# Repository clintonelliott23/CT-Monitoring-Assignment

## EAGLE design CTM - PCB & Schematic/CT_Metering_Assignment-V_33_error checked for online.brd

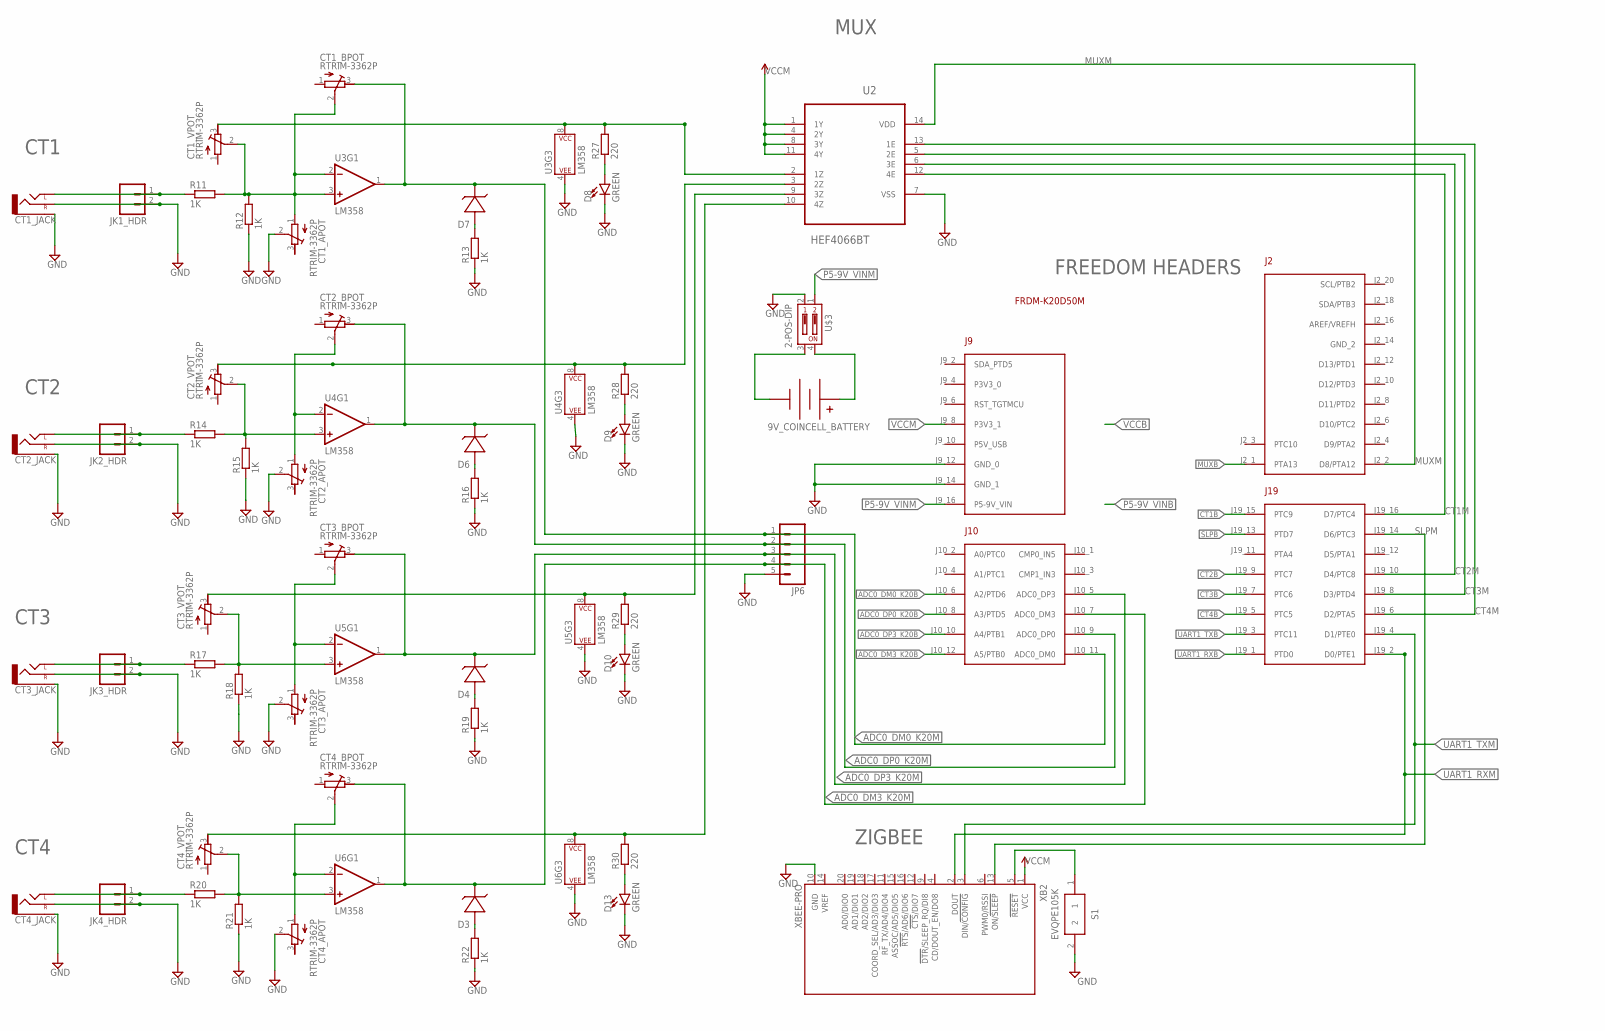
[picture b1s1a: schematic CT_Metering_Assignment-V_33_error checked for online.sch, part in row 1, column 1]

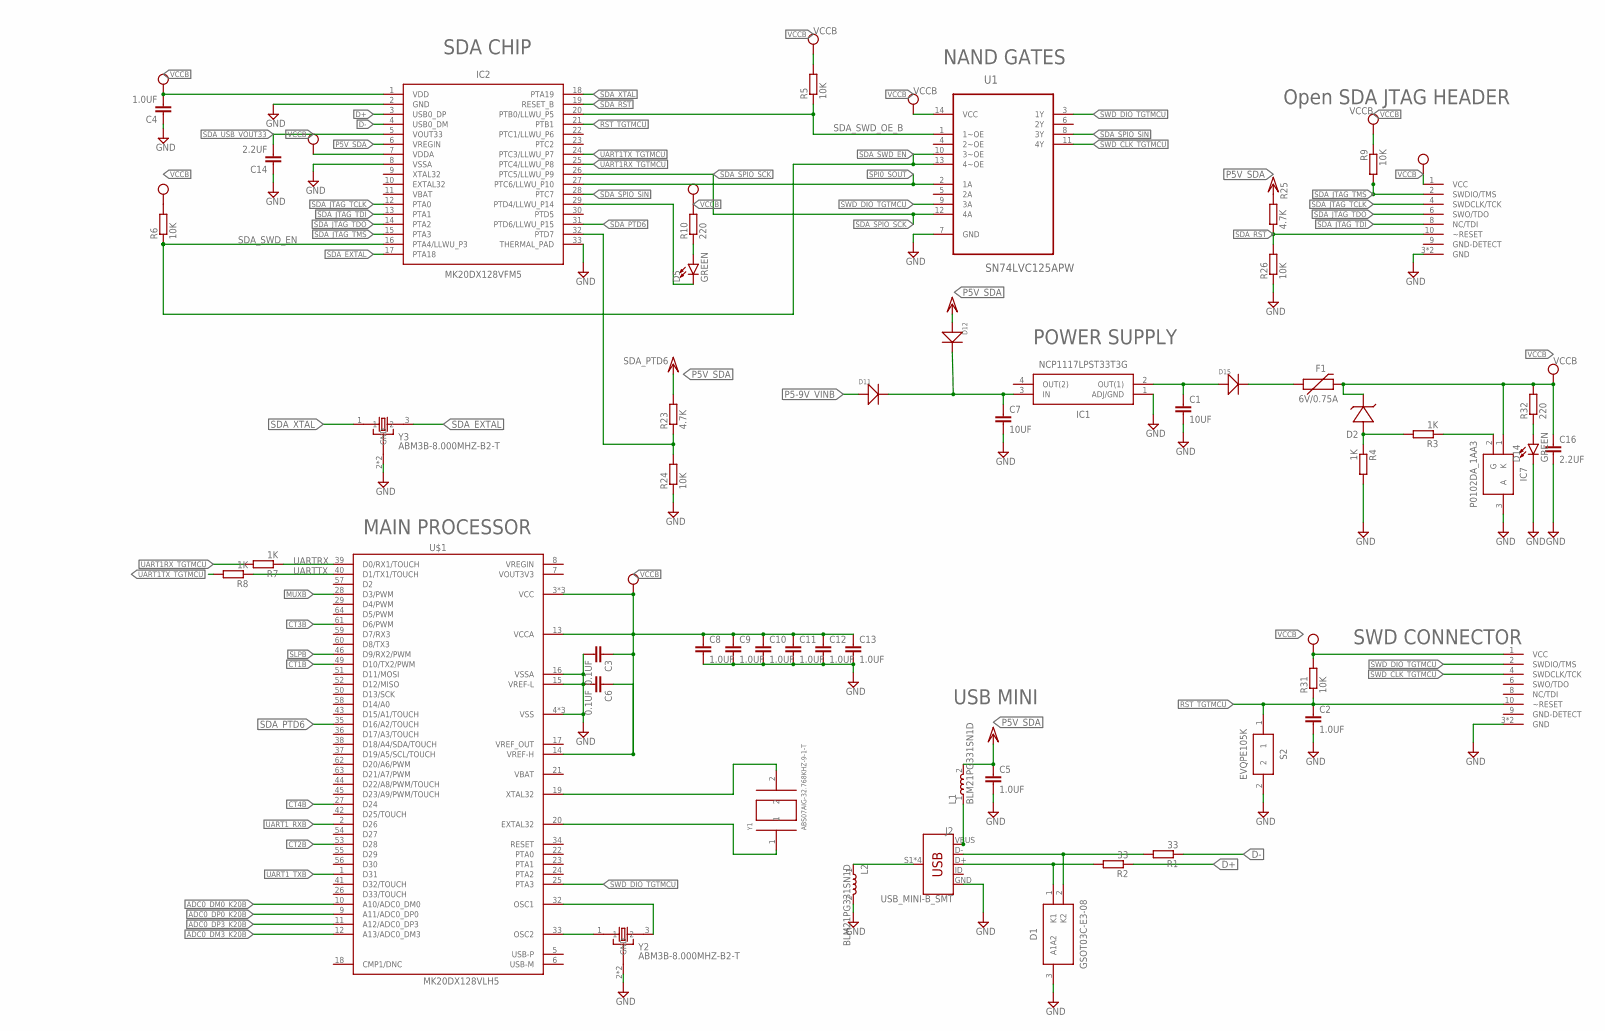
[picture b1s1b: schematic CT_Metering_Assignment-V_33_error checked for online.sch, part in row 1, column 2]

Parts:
9V_COINCELL_BATTERY: BC9VPC
C1, C7: 10UF; C1210
C2, C4, C5, C8, C9, C10, C11, C12, C13: 1.0UF; C1210
C3, C6: 0.1UF; C1210
C14, C16: 2.2UF; C1210
CT1_APOT, CT1_BPOT, CT1_VPOT, CT2_APOT, CT2_BPOT, CT2_VPOT, CT3_APOT, CT3_BPOT, CT3_VPOT, CT4_APOT, CT4_BPOT, CT4_VPOT: RTRIM-3362P; RTRIM3362P
CT1_JACK, CT2_JACK, CT3_JACK, CT4_JACK: AUDIO-JACKPTH; AUDIO-JACK
D1: GSOT03C-E3-08; SOT100P248X115-3N
D2, D3, D4, D6, D7: ZENER; SOD123
D5, D8, D9, D10, D13, D14: GREEN; LED-0603
D11, D12, D15: 20V-1A; SOD-123
F1: 6V/0.75A; 1206
FRDM1: FRDM-K20D50M
IC1: NCP1117LPST33T3G; SOT230P700X180-4N
IC2: MK20DX128VFM5; SOT617-14
IC7: P0102DA_1AA3; TO-92
J2: USB_MINI-B_SMT; USB-MINIB
JK1_HDR, JK2_HDR, JK3_HDR, JK4_HDR: M02PTH; 1X02
JP6: M05PTH; 1X05
L1, L2: BLM21PG331SN1D; INDC2012X87
R1, R2: 33; PRL1632
R3, R4, R7, R8, R11, R12, R13, R14, R15, R16, R17, R18, R19, R20, R21, R22: 1K; PRL1632
R5, R6, R9, R24, R26, R31: 10K; PRL1632
R10, R27, R28, R29, R30, R32: 220; PRL1632
R23, R25: 4.7K; PRL1632
S1, S2: EVQPE105K; EVQPE1
U1: SN74LVC125APW; SOP65P640X120-14N
U2: HEF4066BT; SOIC127P600X175-14N
U3, U4, U5, U6: LM358; DIP08
U$1: MK20DX128VLH5; QFP50P1200X1200X160-64N
U$2: 2X5_0.05"_CORTEX_DEBUGTH_NOKEY_UNSHROUDED; 2X5_0.05"_TH_NS
U$3: 2-POS-DIP; CHS-02A
U$6: SWD HHEADER; 2X5_0.05"_TH_NS
XB2: XBEE-PRO
Y1: ABS07AIG-32.768KHZ-9-1-T; XTAL320X150X90
Y2, Y3: ABM3B-8.000MHZ-B2-T; OSCSC500X320X110-4N

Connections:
ADC0_DM0_K20B: FRDM1.J10_6 (A2/PTD6), U$1.10 (A10/ADC0_DM0)
ADC0_DM0_K20M: CT1_BPOT.3, D7.C (-), FRDM1.J10_11 (ADC0_DM0), JP6.1, U3.1 (OUT)
ADC0_DM3_K20B: FRDM1.J10_12 (A5/PTB0), U$1.12 (A13/ADC0_DM3)
ADC0_DM3_K20M: CT4_BPOT.3, D3.C (-), FRDM1.J10_7 (ADC0_DM3), JP6.4, U6.1 (OUT)
ADC0_DP0_K20B: FRDM1.J10_8 (A3/PTD5), U$1.9 (A11/ADC0_DP0)
ADC0_DP0_K20M: CT2_BPOT.3, D6.C (-), FRDM1.J10_9 (ADC0_DP0), JP6.2, U4.1 (OUT)
ADC0_DP3_K20B: FRDM1.J10_10 (A4/PTB1), U$1.11 (A12/ADC0_DP3)
ADC0_DP3_K20M: CT3_BPOT.3, D4.C (-), FRDM1.J10_5 (ADC0_DP3), JP6.3, U5.1 (OUT)
CT1B: FRDM1.J19_15 (PTC9), U$1.49 (D10/TX2/PWM)
CT1M: FRDM1.J19_16 (D7/PTC4), U2.12 (4E)
CT1_PWR: CT1_VPOT.3, R27.2, U2.2 (1Z), U3.8 (P$V+)
CT2B: FRDM1.J19_9 (PTC7), U$1.53 (D28)
CT2M: FRDM1.J19_10 (D4/PTC8), U2.6 (3E)
CT2_PWR: CT2_VPOT.3, R28.2, U2.3 (2Z), U4.8 (P$V+)
CT3B: FRDM1.J19_7 (PTC6), U$1.61 (D6/PWM)
CT3M: FRDM1.J19_8 (D3/PTD4), U2.5 (2E)
CT3_PWR: CT3_VPOT.3, R29.2, U2.9 (3Z), U5.8 (P$V+)
CT4B: FRDM1.J19_5 (PTC5), U$1.27 (D24)
CT4M: FRDM1.J19_6 (D2/PTA5), U2.13 (1E)
CT4_PWR: CT4_VPOT.3, R30.2, U2.10 (4Z), U6.8 (P$V+)
D+: IC2.3 (USB0_DP), R2.1
D-: IC2.4 (USB0_DM), R1.1
EXTAL32: U$1.20 (EXTAL32), Y1.1
GND: C1.2, C2.2, C3.2, C4.1, C5.2, C6.2, C7.2, C8.2, C9.2, C10.2, C11.2, C12.2, C13.2, C14.1, C16.2, CT1_APOT.2, CT1_JACK.RING (RIGHT), CT1_JACK.SLEEVE, CT2_APOT.2, CT2_JACK.RING (RIGHT), CT2_JACK.SLEEVE, CT3_APOT.2, CT3_JACK.RING (RIGHT), CT3_JACK.SLEEVE, CT4_APOT.2, CT4_JACK.RING (RIGHT), CT4_JACK.SLEEVE, D1.3 (A1A2), D8.C, D9.C, D10.C, D13.C, D14.C, FRDM1.J9_12 (GND_0), FRDM1.J9_14 (GND_1), IC1.1 (ADJ/GND), IC2.2 (GND), IC2.8 (VSSA), IC2.33 (THERMAL_PAD), IC7.3 (A), J2.GND, JK1_HDR.2, JK2_HDR.2, JK3_HDR.2, JK4_HDR.2, JP6.5, L2.2, R4.2, R12.1, R13.1, R15.1, R16.1, R18.1, R19.1, R21.1, R22.1, R24.1, R26.1, S1.2, S2.2, U1.7 (GND), U2.7 (VSS), U3.4 (P$V-), U4.4 (P$V-), U5.4 (P$V-), U6.4 (P$V-), U$1.4 (VSS), U$1.15 (VREF-L), U$1.16 (VSSA), U$1.31 (VSS), U$1.47 (VSS), U$2.3 (GND), U$2.5 (GND), U$3.2, U$6.3 (GND), U$6.5 (GND), XB2.10 (GND), Y2.2 (GND), Y2.4 (GND), Y3.2 (GND), Y3.4 (GND)
MUXB: FRDM1.J2_1 (PTA13), U$1.28 (D3/PWM)
MUXM: FRDM1.J2_2 (D8/PTA12), U2.14 (VDD)
unnamed: 9V_COINCELL_BATTERY.V-, U$3.3
unnamed: C1.1, D15.+, IC1.2 (OUT(1))
unnamed: D6.A (+), R16.2
unnamed: D15.-, F1.1
unnamed: D2.A (+), R3.2, R4.1
unnamed: D7.A (+), R13.2
unnamed: U$1.32 (OSC1), Y2.3 (2)
unnamed: U$1.33 (OSC2), Y2.1
unnamed: J2.S1 (SHIELD), J2.S2 (SHIELD), J2.S3 (SHIELD), J2.S4 (SHIELD), L2.1
unnamed: D4.A (+), R19.2
unnamed: CT2_VPOT.2, R14.2, R15.2, U4.3 (+IN)
unnamed: 9V_COINCELL_BATTERY.V+, U$3.4
unnamed: C7.1, D11.-, D12.-, IC1.3 (IN)
unnamed: D8.A, R27.1
unnamed: D1.2 (K2), J2.D-, R1.2
unnamed: IC7.2 (G), R3.1
unnamed: CT4_APOT.1, CT4_BPOT.2, U6.2 (-IN)
unnamed: D9.A, R28.1
unnamed: D3.A (+), R22.2
unnamed: D1.1 (K1), J2.D+, R2.2
unnamed: D5.C, IC2.29 (PTD4/LLWU_P14)
unnamed: D5.A, R10.1
unnamed: D10.A, R29.1
unnamed: S1.1, XB2.5 (!RESET)
unnamed: D13.A, R30.1
unnamed: CT1_APOT.1, CT1_BPOT.2, CT1_VPOT.2, R11.2, R12.2, U3.2 (-IN), U3.3 (+IN)
unnamed: D14.A, R32.1
unnamed: CT2_JACK.TIP (LEFT), JK2_HDR.1, R14.1
unnamed: CT2_APOT.1, CT2_BPOT.2, U4.2 (-IN)
unnamed: CT1_JACK.TIP (LEFT), JK1_HDR.1, R11.1
unnamed: IC2.32 (PTD7), R23.1, R24.2
unnamed: CT3_JACK.TIP (LEFT), JK3_HDR.1, R17.1
unnamed: CT3_VPOT.2, R17.2, R18.2, U5.3 (+IN)
unnamed: CT3_APOT.1, CT3_BPOT.2, U5.2 (-IN)
unnamed: CT4_JACK.TIP (LEFT), JK4_HDR.1, R20.1
unnamed: CT4_VPOT.2, R20.2, R21.2, U6.3 (+IN)
P5-9V_VINB: D11.+
P5-9V_VINM: FRDM1.J9_16 (P5-9V_VIN), U$3.1
P5V0_SDA_USB: J2.VBUS, L1.1
P5V_SDA: C5.1, D12.+, IC2.6 (VREGIN), L1.2, R23.2, R25.2
RST_TGTMCU: C2.1, IC2.21 (PTB1), R31.1, S2.1, U$6.10 (~RESET)
SDA_EXTAL: IC2.17 (PTA18), Y3.3 (2)
SDA_JTAG_TCLK: IC2.12 (PTA0), U$2.4 (SWDCLK/TCK)
SDA_JTAG_TDI: IC2.13 (PTA1), U$2.8 (NC/TDI)
SDA_JTAG_TDO: IC2.14 (PTA2), U$2.6 (SWO/TDO)
SDA_JTAG_TMS: IC2.15 (PTA3), R9.2, U$2.2 (SWDIO/TMS)
SDA_PTD6: IC2.31 (PTD6/LLWU_P15), U$1.35 (D16/A2/TOUCH)
SDA_RST: IC2.19 (RESET_B), R25.1, R26.2, U$2.10 (~RESET)
SDA_SPIO_SCK: IC2.26 (PTC5/LLWU_P9), U1.12 (4A)
SDA_SPIO_SIN: IC2.28 (PTC7), U1.8 (3Y)
SDA_SWD_EN: IC2.16 (PTA4/LLWU_P3), R6.1, U1.10 (3~OE), U1.13 (4~OE)
SDA_SWD_OE_B: IC2.20 (PTB0/LLWU_P5), R5.1, U1.1 (1~OE)
SDA_USB_VOUT33: C14.2, IC2.5 (VOUT33)
SDA_XTAL: IC2.18 (PTA19), Y3.1
SLPB: FRDM1.J19_13 (PTD7), U$1.46 (D9/RX2/PWM)
SLPM: FRDM1.J19_14 (D6/PTC3), XB2.13 (ON/!SLEEP)
SPI0_SOUT: IC2.27 (PTC6/LLWU_P10), U1.2 (1A)
SWD_CLK_TGTMCU: U1.11 (4Y), U$6.4 (SWDCLK/TCK)
SWD_DIO_TGTMCU: U1.3 (1Y), U1.9 (3A), U$1.25 (PTA3), U$6.2 (SWDIO/TMS)
UART1RX_TGTMCU: IC2.25 (PTC4/LLWU_P8), R7.2
UART1TX_TGTMCU: IC2.24 (PTC3/LLWU_P7), R8.2
UART1_RXB: FRDM1.J19_1 (PTD0), U$1.2 (D26)
UART1_RXM: FRDM1.J19_2 (D0/PTE1), XB2.2 (DOUT)
UART1_TXB: FRDM1.J19_3 (PTC11), U$1.1 (D31)
UART1_TXM: FRDM1.J19_4 (D1/PTE0), XB2.3 (DIN/!CONFIG)
UARTRX: R7.1, U$1.39 (D0/RX1/TOUCH)
UARTTX: R8.1, U$1.40 (D1/TX1/TOUCH)
VCCB: C3.1, C4.2, C6.1, C8.1, C9.1, C10.1, C11.1, C12.1, C13.1, C16.1, D2.C (-), F1.2, IC2.1 (VDD), IC2.7 (VDDA), IC7.1 (K), R5.2, R6.2, R9.1, R10.2, R31.2, R32.2, U1.14 (VCC), U$1.3 (VCC), U$1.13 (VCCA), U$1.14 (VREF-H), U$1.30 (VCC), U$1.48 (VCC), U$2.1 (VCC), U$6.1 (VCC)
VCCM: FRDM1.J9_8 (P3V3_1), U2.1 (1Y), U2.4 (2Y), U2.8 (3Y), U2.11 (4Y), XB2.1 (VCC)
XTAL32: U$1.19 (XTAL32), Y1.2

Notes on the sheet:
CT1
CT2
CT3
CT4
FREEDOM HEADERS
ZIGBEE
MUX
SWD CONNECTOR
USB MINI
POWER SUPPLY
SDA CHIP
NAND GATES
MAIN PROCESSOR
Open SDA JTAG HEADER

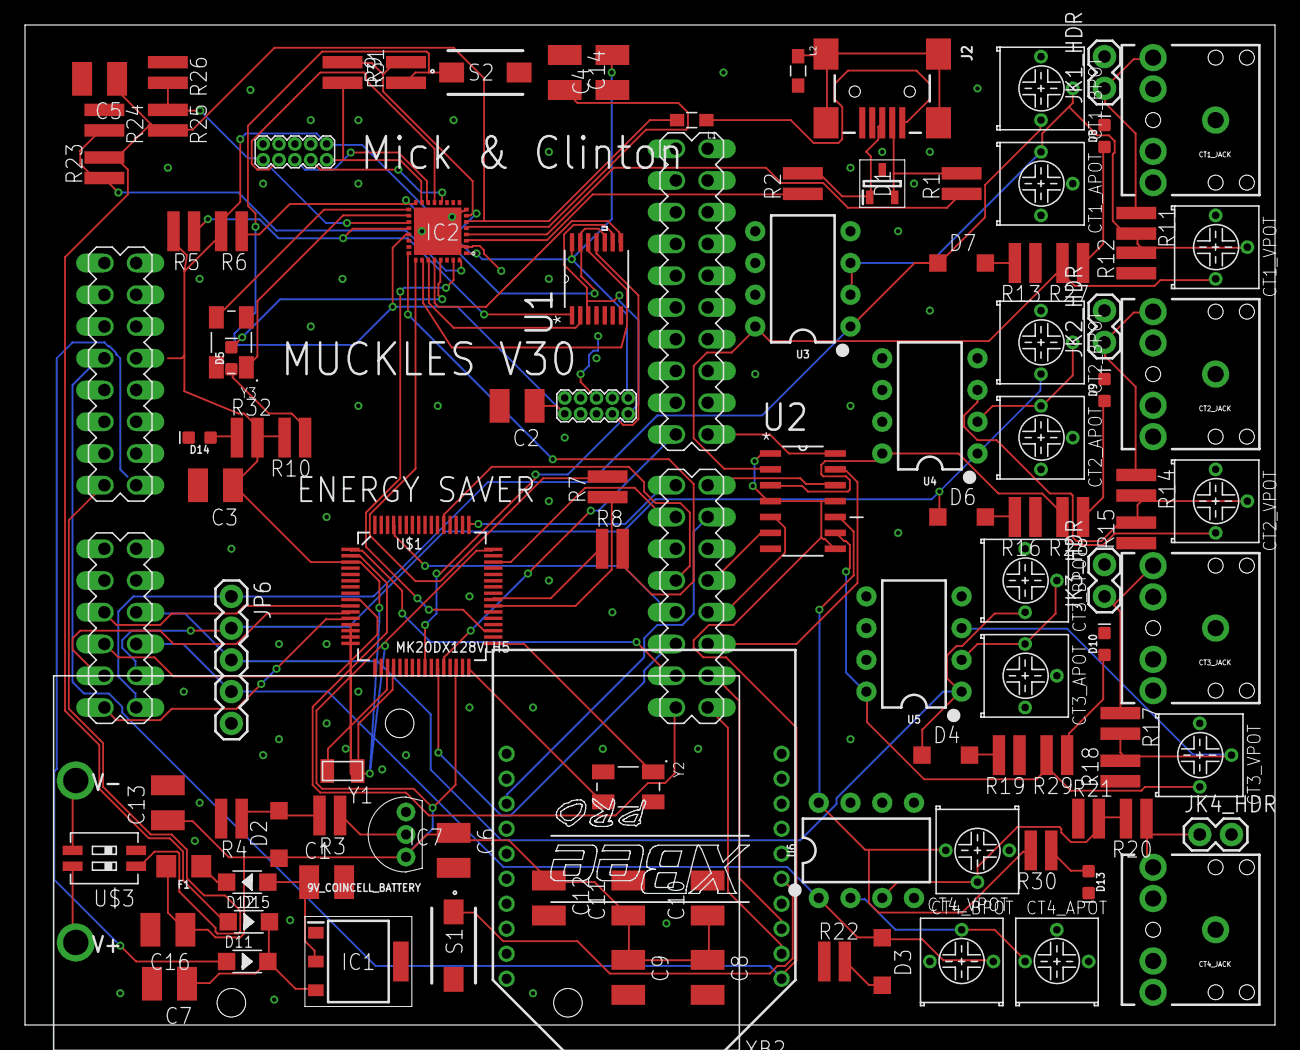
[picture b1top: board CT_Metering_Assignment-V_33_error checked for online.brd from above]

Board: 2 copper layers, 100.0 x 80.0 mm, 108 parts (0 on the bottom side), 95 nets.

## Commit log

2017-08-28 Information for Assignment
    Task sheet and Information
2017-08-28 Setup File for Schematic
    Eagle file with frame
2017-08-30 Learned Altium
    Started with Schematic Design and how to use Alitum
    Imported Libraries
    Have question about mirroring...
2017-08-30 Jake showed how to mirror
2017-08-30 moved component
2017-08-30 moved also
2017-08-30 Moved Back
2017-08-31 Have to update each time
2017-09-04 OK CHECK AGAIN
2017-09-04 Updated things
2017-09-04 added folder
2017-09-05 Started Kinetis Code for CT
2017-09-05 Created CT Schematic
    :)
2017-09-05 Cleaned up folder
2017-10-29 Updated all shit
    ***Need to finish report
2017-10-29 Need to Proof Report
    Mick is finishing off manual :)
2017-10-29 Finished Report
    Need to Finish Manual
2017-10-30 FINISHED BRA
2017-10-30 Added two schematids pDFs

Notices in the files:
parts and their libraries:
SparkFun-Connectors: Licensing: Creative Commons ShareAlike 4.0 International - https://creativecommons.org/licenses/by-sa/4.0
